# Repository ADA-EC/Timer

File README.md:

# Timer
Um temporizador de tomada simples, apenas usando portas lógicas, contadores e relé

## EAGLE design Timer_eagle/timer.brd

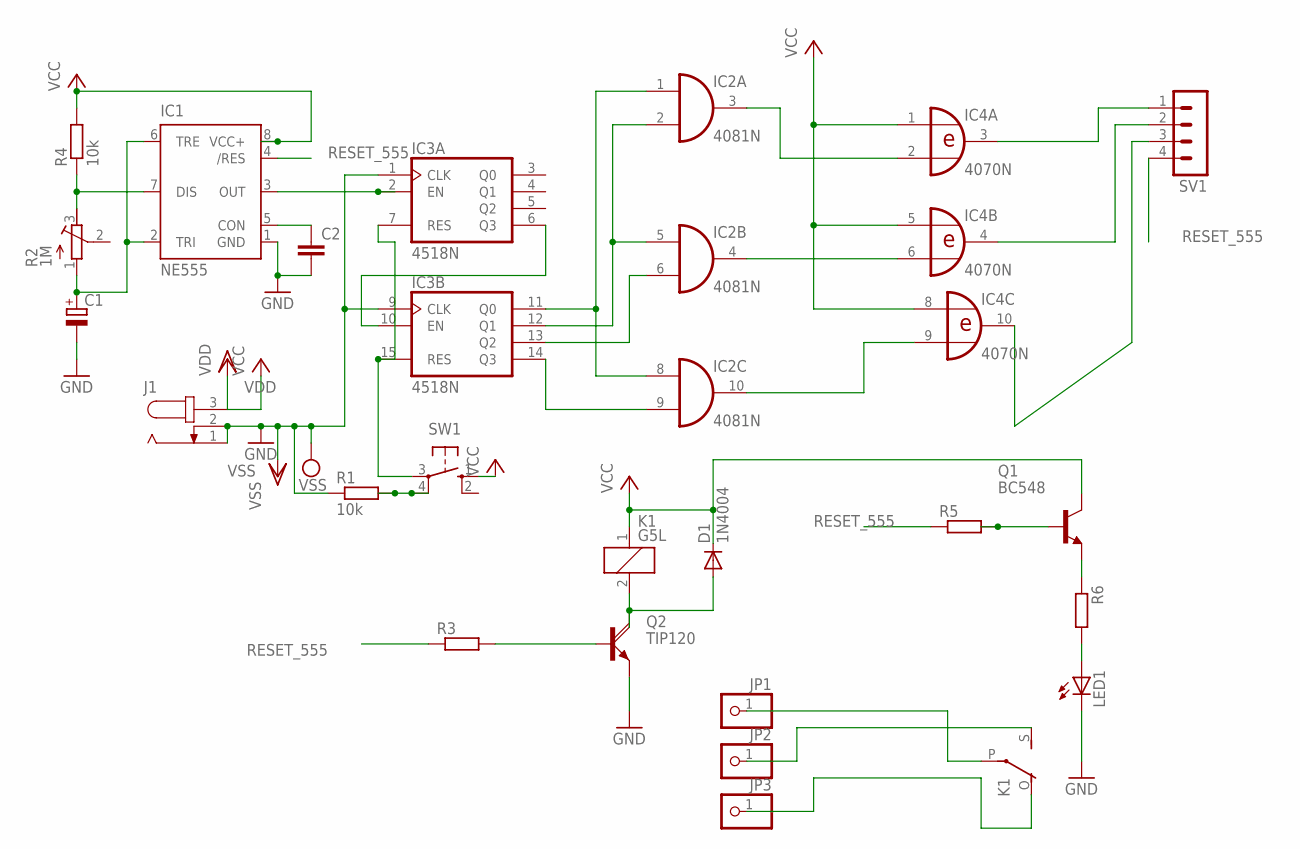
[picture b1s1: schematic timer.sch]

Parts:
C1: CPOL-EUE2.5-6; E2,5-6
C2: C-EU025-024X044; C025-024X044
D1: 1N4004; DO41-10
IC1: NE555; DIL-08
IC2: 4081N; DIL14
IC3: 4518N; DIL16
IC4: 4070N; DIL14
J1: JACK-PLUG0; SPC4077
JP1, JP2, JP3: PINHD-1X1; 1X01
K1: G5L; G5LE
LED1: LED_ELD260; LED_LD260
Q1: BC548; TO92-EBC
Q2: TIP120; TO220AH
R1, R4: 10k; 0207/10
R2: 1M; RTRIM64W
R3, R5, R6: R0207/10; 0207/10
SV1: MA04-1
SW1: 10-XX; B3F-10XX

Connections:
unnamed: C1.+, IC1.2 (TRI), IC1.6 (TRE), R2.1 (A)
unnamed: IC1.3 (OUT), IC3.2 (EN)
unnamed: Q2.B, R3.2
unnamed: IC1.7 (DIS), R2.3 (E), R4.1
unnamed: R1.2, SW1.4 (P1)
unnamed: IC3.7 (RES), IC3.15 (RES), SW1.3
unnamed: C2.1, IC1.5 (CON)
unnamed: IC2.1 (I0), IC2.8 (I0), IC3.11 (Q0)
unnamed: IC2.2 (I1), IC2.5 (I0), IC3.12 (Q1)
unnamed: IC2.6 (I1), IC3.13 (Q2)
unnamed: IC2.9 (I1), IC3.14 (Q3)
unnamed: IC4.3 (O), SV1.1
unnamed: IC2.10 (O), IC4.9 (I1)
unnamed: IC4.10 (O), SV1.3
unnamed: IC4.4 (O), SV1.2
unnamed: D1.A, K1.2, Q2.C
unnamed: IC2.3 (O), IC4.2 (I1)
unnamed: IC2.4 (O), IC4.6 (I1)
unnamed: JP1.1, K1.P
unnamed: JP2.1, K1.S
unnamed: JP3.1, K1.O
unnamed: Q1.B, R5.2
unnamed: LED1.A, R6.2
unnamed: Q1.E, R6.1
Q3_EN2: IC3.6 (Q3), IC3.10 (EN)
RESET_555: IC1.4 (/RES), R3.1, R5.1, SV1.4
VDD: D1.C, IC1.8 (VCC+), IC2.14 (VDD), IC3.16 (VDD), IC4.1 (I0), IC4.5 (I0), IC4.8 (I0), IC4.14 (VDD), J1.3, K1.1, Q1.C, R4.2, SW1.1 (S)
VSS: C1.-, C2.2, IC1.1 (GND), IC2.7 (VSS), IC3.1 (CLK), IC3.8 (VSS), IC3.9 (CLK), IC4.7 (VSS), J1.1, J1.2, LED1.K (C), Q2.E, R1.1

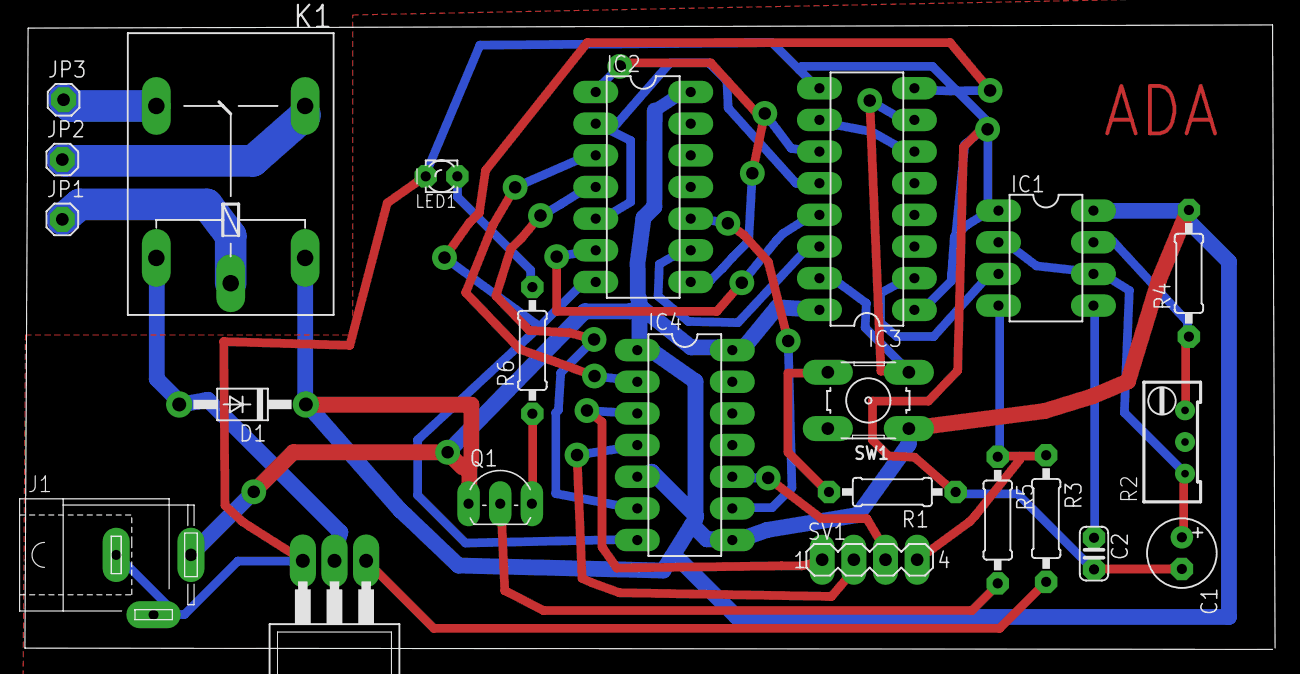
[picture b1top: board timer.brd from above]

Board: 2 copper layers, 100.3 x 50.1 mm, 23 parts (0 on the bottom side), 28 nets.

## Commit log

2016-10-29 Lista os componentes utilizados na montagem do timer
2016-10-29 Projeto no eagle do timer
2016-10-30 A parte do oscilador e do contador estão monstadas no esquemático
2016-10-31 O esquematico do projeto está finalizado
2016-10-31 Alguns erros no esquemático foram consertados
2016-10-31 O projeto da plva está atualizado
2016-10-31 O projeto da placa está atualizado
2016-10-31 Projeto atualizado da placa
2016-11-05 As trilhas de alimentação foram engrssadas, e a placa foi completada com o terra
2016-11-17 Projeto final da placa
2016-11-21 Todas as trilhas e pads foram engrossados
2016-11-22 Esquemático Corrigido (Ligação RES_555) Projeto da Placa refeito
2016-11-22 As trilhas foram engrossadas, o VCC foi ligado com o VDD, o VSS foi ligado com o GND
